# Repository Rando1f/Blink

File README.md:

# Blink
Blink is a desk tracking device that tracks the user's time spent on the desk per session, displaying different animations based on how long the user has been going for. It uses an ultrasonic sensor that measures the distance between the user and itself. If that distance was lower than 15 in., it tracks that the user has been sitting on his desk. If it is more than 15 in., it tracks that the user is away from his desk. 
the animation are vresions of the same mascot "rando1f"

### Used appication
multiple applications were used in the creatino of blink starting with 
<ul>
    <li>piskel: for animated pixelated gifs</li>
    <li>wokwi: for basic connection simulations</li>
    <li>Kicad: for PCB creation</li>
    <li>Auto desk fusion360: for the case creation</li>
    <li>VS code: for writing code and uploading it to the esp32   *must be paired with platformio extension</li>
</ul>

### How to use blink
Blink's code is meant to be flashed into an ESP32. This could be done through buying the PCP that was published in [production](production) here through the Gerber files, or through using a breadboard with the following wiring.This is going to be done through VS Code and PlatformIO or Arduino IDE, although I recommend using Visual Studio Code because it offers an easier time debugging or adding features if you want to.  

blink is plugged into the users device through a micro-usb port that has clearance of about 0.5 mm in the case and is mounted on the bottom of your desk after you screw the lid with body of the case either through superglue or a doubled face tape since blink is fairly light.

### pcb 
BLINK PCB is built on the wiring showcased in the How to use BLINK section, where it links all of the components to an NGND with an OLED screen having a 3.3 V input with normal I2C protocol wiring, which is SDA: pin 21 and SCL: pin 22.
on the other hand HC-SR04 Has a VIN or a 5V input, and due to the ESP32's 3.3V capacity, a voltage divider of two resistors: Resistor 1 being 220, Resistor 2 being 330, To bring the voltage down towards the 3V, so it doesn't fry or break the ESP32 with default wiring of trig: pin 5 and echo: pin 18.  
the esp32 used in this project was esp32 devkit 30pin.
the dimensions of the pcb are: 74.93*85.55*20

<table>
<tr>
    <td width="50%">
.</td>
    <td width="50%"> </td>
</tr>
</table>

### Case
the case was done with rough parts mesurments (beside the pcb with a 0.2mm tolarnce) and a casse thickness of 10mm.
the case features an ultrasonic sensor opening and an oled screen display cut extrusion where the oled screen would lie on a 90 degree angle with it being connecetd to the pcb trough jumper wires.
there are 4 studs on the 4 corners on the inside of the case to have a 3mm clearance below for all of the conections.
the case dimensions: 95.13mm *105.75mm *35 mm
the oled display dimensions: 20 mm* 27 mm
hc-sro4 diameter: 20

#### AI use

AI was only used for research purposes, and it wasn't used excessively. Rather, it was used as a resource-gathering tool so I could understand more of the project. The read.me is fully human-written, as well as the journal and the bill of materials.

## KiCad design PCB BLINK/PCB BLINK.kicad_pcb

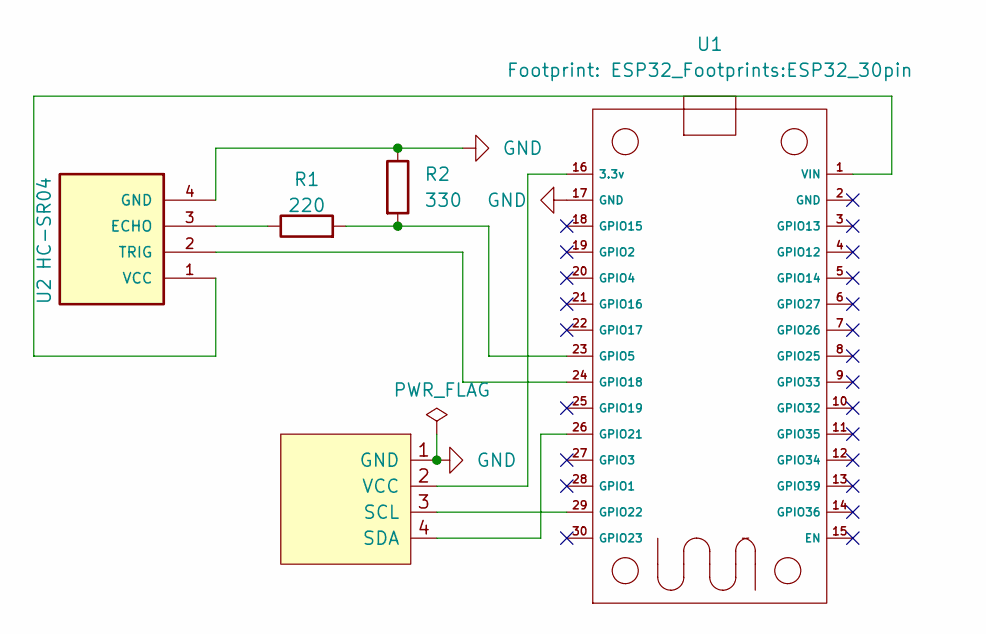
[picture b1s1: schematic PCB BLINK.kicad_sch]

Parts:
Brd1: SSD1306; 128x64OLED
R1: 220; R_Axial_DIN0207_L6.3mm_D2.5mm_P10.16mm_Horizontal
R2: 330; R_Axial_DIN0207_L6.3mm_D2.5mm_P10.16mm_Horizontal
U1: ESP32_30pin
U2: HC-SR04; XCVR_HC-SR04

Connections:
GND: Brd1.1 (GND), R2.1, U1.17 (GND), U2.4 (GND)
unnamed: Brd1.3 (SCL), U1.29 (GPIO22)
unnamed: Brd1.4 (SDA), U1.26 (GPIO21)
unnamed: Brd1.2 (VCC), U1.16 (3.3v)
unnamed: R1.2, R2.2, U1.23 (GPIO5)
unnamed: U1.24 (GPIO18), U2.2 (TRIG)
unnamed: U1.1 (VIN), U2.1 (VCC)
unnamed: R1.1, U2.3 (ECHO)

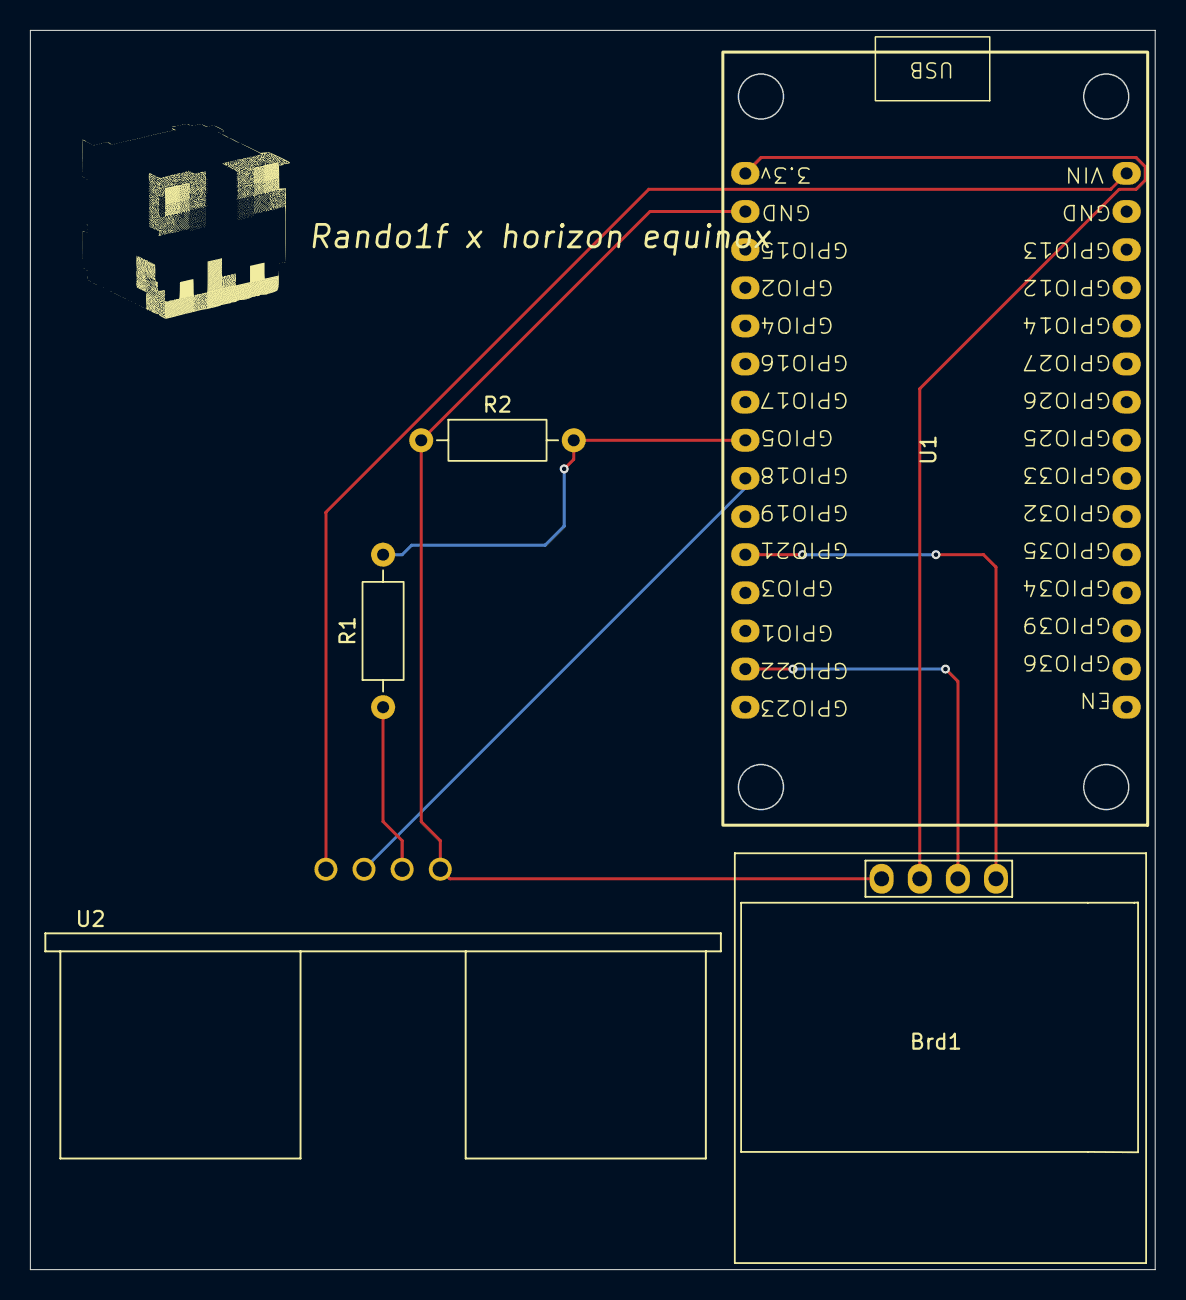
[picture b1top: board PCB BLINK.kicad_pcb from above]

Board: 2 copper layers, 74.9 x 82.6 mm, 5 parts (0 on the bottom side), 8 nets.
